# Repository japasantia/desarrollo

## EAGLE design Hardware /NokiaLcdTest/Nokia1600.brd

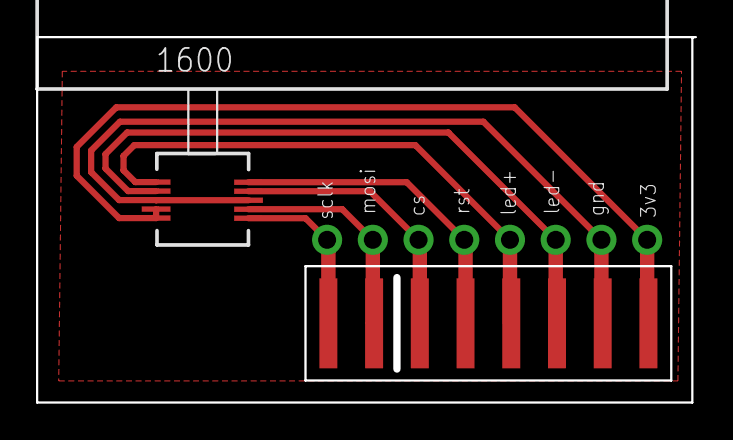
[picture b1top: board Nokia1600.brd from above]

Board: 2 copper layers, 36.6 x 20.3 mm, 3 parts (0 on the bottom side), 8 nets.

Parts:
EDGE1: CARD-EDGE-8P; DUOPLUG-8P-KEYED
JP1: 1X08_ROUND
U$1: NOKIA1600_LCD

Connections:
CLK: EDGE1.1, JP1.1, U$1.1
CS: EDGE1.3, JP1.3, U$1.4
GND: EDGE1.7, JP1.7, U$1.3, U$1.8
LED+: EDGE1.5, JP1.5, U$1.6
LED-: EDGE1.6, JP1.6, U$1.7
RESET: EDGE1.4, JP1.4, U$1.5
SDA: EDGE1.2, JP1.2, U$1.2
VCC: EDGE1.8, JP1.8, U$1.9, U$1.10

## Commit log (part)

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2017-05-26 Respaldo inicial en Desarrollo
    Se abre el repositorio (nuevamente)
2017-05-29 Commit de respaldo
    Se hace commit masivo para respaldo
2017-06-01 Commit respaldo
    - Trabajo en pruebas de librerias VISA
    - Proyectos desarrollo actualizados
2017-06-06 Pruebas para adaptar libreria <linux-gpib> a Java, por medio de JNA. Respaldo
2017-06-10 Commit para sincronizar repositorios y respaldo
    Se han hecho cambios en PC-casa que no ha sido enviados al repositorio remoto.
2017-06-14 Se modifica archivo de proyecto libreria GPIB en Java
    - Modificación en interfaz ILinuxGPIB
2017-06-15 Respaldo, cambio de nombre archivos
2017-06-16 Trabajo en CenditLab, proyecto Communications
    - Modificacion CommunicationAbstractionLayer
2017-06-19 Trabajo en CenditLab
    - Modificaciones en torno a VisaAddress
2017-06-19 Respaldo de archivo VisaAddress.java para resolver problema de sincronia de repos (rebase)
2017-06-20 Trabajo en CenditLab, Communications - VisaAddress - GpibConnection - Excepciones
2017-06-21 Modificaciones en CenditLab.Communications
    Trabajo en capa comunicaciones GPIB
    - GpibConnection
    - VisaAddress
2017-06-26 Modificacion libreria TFT LCD para PIC18
    - Modificacion módulo TftLcdIO para adaptarlo a los puertos de PIC18F4550
    - Definicion de pines
    - Modificacion de rutinas inicializacion
2017-06-29 Modificaciones en firmware PIC
    - Cendit HID bootloader: resuelto problema con boton booloader
    - Modificados algunos proyectos PIC18 USB
2017-06-29 Trabajo en Communications
    - Wrapper libreria VXI11
    - Prueba de conexion exitosa con VXI11
2017-06-30 Actualizacion de Communications en CenditLab
    - Agregados coentarios relativos a libreria VXI11
    - Trabajo en clase Vxi11Connection
2017-07-07 Trabajo en desarrollo: CenditLab + Pic
    - En CenditLab inicia desarrollo adaptadores Visa.
    - Modificaciones a proyecto PIC pic_lcd.
2017-07-11 Se agregan dos proyectos en desarrollo
    - Modificación del proyecto Cendit Hid Bootloader
    - Nuevo proyecto pic_serial_pc: consola serial para la tarjeta CenditBoard
2017-07-14 Trabajo en desarrollo: CenditLab
    - Continua desarrollo librearia Measurments, agregadas nuevas clases
    - Modificaciones en proyectos PIC
    - Se agregan proyectos prueba librerias de comunicacion serial
2017-07-17 Modificaciones en proyectos y limpieza directorios
    - Cambios en pic_lcd
    - Revision PicSerial
    - Revision cendit_hid_bootloader_pc
2017-07-18 Modificacion en proyecto pic_cd
    - Modificacion hecha para pruebas con libreria TFT LCD.
    - Respaldo de proyectos modificados anteriormente
2017-07-20 Modificacion en proyectos: pic_serial y pic_lcd
    - Cambios UI en pic_serial + nuevos comandos para probar libreria LCD
2017-07-20 Trabajo en CenditLab, replanteo de clases
    - Se replantea clase ScpiCommands, 3era prueba
2017-07-21 Modificaciones en CenditLab: Measurements y Communications
    - Se reimportan el proyectos, modificaciones en archivos proyecto, manifiestos.
    - Se refina ScpiCommand3
    - Modificadas clases relativas a Task, solo para poder compilar
2017-07-25 Trabajo en pic_lcd y PicSerial
    - Correcciones en libreria PIC LCD, ahora funciona
    - PicSerial utilidad para pruebas libreria PIC LCD, version inicial
2017-07-25 Se inicia proyecto pic_seial_32
    - Proyecto en Qt 5.2 32 bits.
2017-08-02 Commit respaldo
    - Libreria pic_lcd funcional
2017-08-15 Inicia desarrollo de CenditBoard, tarjeta reducida
2017-08-17 CenditLab, prueba nuevo concepto para organizar tareas y sus datos de in/out
    - Se idea un nuevo concepto para el manejo de datos de las tareas.
    - Clase Value, representa argumento de una tarea.
    - Nueva definicion de interfaz Task (Task2).
2017-08-18 Respaldo ultima hora
    - Proyecto Kicad tarjeta Cendit11713, v2
2017-08-23 Respaldo, trabajo en desarrollo de software+hardware
    - En hardware, tarjeta control puertos Viking (Shift register port exp)
    - En software edición ligera en CenditLab
2017-08-24 Trabajo en desarrollo CenditLab + hardware Cendit11713
    - Modulo Task, se crea clases para menejo de Instrumentos (Instrument)
    - Ediciones de esquematicos Cendit11714 + tarjeta Nokia 1600 LCD
2017-08-30 CenditLab, modulo Communications
    - Se importa modulo Communications
    - Proceso de revision y refactor de clases
    - Se crea instalador para pruebas, inicialmente instala modulo Views
2017-08-31 CenditLab, modulo Communications
    - Prosigue la revision de clases: Gpib + Vxi
    - Manejo de excepciones, creacion clase base CommunicationException
    - Pruebas exitosas
2017-09-05 CenditLab, trabajo GUI modulo Views + nuevos tipos de datos en Task
    - Se agregan vistas para arreglos (ArrayData)
    - Boton para barra de navegacion
    - Se agregan tipo de datos ArrayData en Tasks
2017-09-06 CenditLab, trabajo en Communications + Views
    - Comunications, revision + correcciones correspondientes a Vxi11
    - Views, modificaciones en ArrayDataView
2017-09-08 CenditLab, modulo Views + Tasks
    - En Views se agrega widget para graficos XY
    - En Tasks se corrigen fallas en clase ArrayData
2017-09-12 En CenditLab
    - Se modifica control GraphView para acoplarse con GraphData
    - Se renombran clases
    - Pruebas satisfactorias
2017-09-13 En CenditLab se trabaja en concepto para manejo de session de medicion
    - Se crean clases MeasurementSession y MeasurementStep
    - Pruebas con GUI y vistas
2017-09-14 Commit para respaldo ultima hora
2017-09-18 En CenditLab modificaciones en modulos Tasks + Views
    - Edicion de clases MeasurementSession y MeasurementStep
    - Creacion de objetos view StepsBarView y StepButtonView
    - Creacion de archivos fxml respectivos
2017-09-19 CenditLab + footprints PCB
    - En CenditLab se trabaja en UI Views, se crea ContainerWindow
    - Se realizan ajustes en StepButton y StepsBarView
    - Se crea footprint conector SATA
2017-09-21 CenditLab + esquematicos + PCB
    - En CenditLab creadas clases de vistas (Views)
    - Se crean footprints
2017-09-21 Commit adicional al anterior, respaldo
2017-09-27 CenditLab + Cendit11713 multiples cambios desarrollo software + hardware
    - CenditLab revision + reformulacion + refactor de clases
    - Cendit11713 creacion de footprints + esquematico controlador de teclado
2017-09-28 En CenditLab trabajo en modulo Views
    - Forma mas eficiente de generar vistas
    - Organizacion de vistas en filas y columnas
    - Clases RowContainerView + ColumnContainerView
2017-09-29 Trabajo en CenditLab
    - Clases para el organizacion de vistas en filas-columnas
2017-10-08 Trabajo en CenditLab.Reducido + Cendit11713
    - CenditLab componenets GUI setup frecuencia
    - Cendit11713 esquematicos expansor puerto GPIB
2017-10-09 En CenditLab.Reducido
    - Clases manejo de paneles y valores de frecuencia actualizados
2017-10-10 En CenditLab.Reducido
    - Modificacion y refactor de clases Field (FrequencyValue -> FrequencyField)
2017-10-10 Cendit11713: Trabajo en esquematicos + PCB
    - Se editan esquematicos expansor IO Viking
    - Creada tarjeta PCB adaptador multipuertos
2017-10-13 Trabajo en CenditLab.Reducido + Cendit17713 PCB
    - Clases paneles UI modificados
    - Clases para manejo y validacion de datos
    - PCB expansor puertos Viking
2017-10-16 Trabajo en CenditLab + Cendit11713 PCB
    - Clases UI entrada de ENR + archivos fxml
    - Expansor puertos Viking
    - Controlador teclado capacitivo
2017-10-17 Trabajo en CenditLab.Reducido + Cendit11713 PCB
    - CenditLab clases para manejo de setup ENR
    - Clase field para dato temperatura
    - Edición de PCBs Capacitive Keyboard
    - Edición de esquematico MainBoard con PIC18F4550 DIP
2017-10-19 Para Cendit11713 creacion de footprints
    - Interruptores luminosos
    - Sensor humedad SI70201
    - Sensor de presion MPL3115A2
2017-10-20 Cendit11713 respaldo del trabajo en PCBs
2017-10-20 En CendiLab edicion de archivo UI + Respaldo
    - Edicion de fxl para setup
    - Respaldo de archivos esquematicos + PCB
2017-10-22 CenditLab.Reducido respaldo de archivos
    - Archivos .java EnrSetup, FrequencySetup, TemperatureField
2017-10-24 En CenditLab.Reducido
    - Trabajo en clases FrequencySetup + FrequencySetupView.
    - Pruebas satisfactorias
2017-10-26 En CenditLab.Reducido + respaldo archivos Gerber
    - Se retoman clases de antiguo CenditLab
    - Clases relativas a MeasurementManager + MeasurementStep
    - Vista MeasurementBarView + StepButtonView
    - Se respaldan archivos Gerber
2017-10-27 En CenditLab.Reducido + Respaldo
    - Correccion de clase relativas a FieldsView (FieldInput + Field)
    - Respaldo de archivos Cendit11713 (esquematicos + PCB)
    - Respaldo diseño fuente: creado hoy
2017-10-31 En CenditLab: gestion de proceso de medicion en UI + pruebas
    - Clase que representa sistema-dispositivo NFA (System)
    - Clases que representan pasos de medicion (MeasurementStep)
    - Clases tareas asosciadas a NFA (Task)
2017-10-31 En CenditLab trabajo en vistas para setup
    - Clase SetupContainerView vista para configuracion
    - Nueva organizacion de modulos/directorios
    - Se debio reimportar proyectos
2017-11-01 En CenditLab.Reducido + Cendit11713
    - Clase para manejo setup frecuencia basico (BasicFrequencySetup)
    - Archivo fxml para esta clase
    - Correciones en FieldInput
    - Creada simulacion Multisim para high side driver
2017-11-02 Cendit11713 + aparecen modificadas clases Java
    - Diseño de high side driver simulacion Multisim
    - Aparecen modificadas clases Java BasicFrequencySetup, aunque no se hayan tocado
2017-11-02 En CenditLab.Reducido + Cendit11713
    - Clase para vista generica - contenedor top level (GenericMainView)
    - Simulación de un high side driver Multisim
2017-11-07 En CenditLab.Reducido + respaldo de esquematicos + PCBs
    - Clases vistas para cada paso de medicion
    - Respaldo de archivos Cendit11713 (esquematicos + PCBs)
2017-11-08 En CenditLab.Reducido + Cendit11713
    - Para CenditLab vistas para Steps + fabrica de vistas ComponentViewfactory
    - En Cendit11713 revision PCB VikingPortExpander + Gerber
2017-11-09 En CenditLab.Reducido + respaldo de Cendit11713
    - Clases fabrica de vistas ComponentViewFactory
    - Modificacion de clases MeasurementStep
    - Respaldo de archivos esquematicos + PCBs Cendit11713 (sin editar)
2017-11-10 Revision + correccion en CenditLab.Reducido + respaldo diseño hardware
    - Revisadas clases y archivos fxml + correcciones
    - No se modifican archivos hardware pero se respaldan
2017-11-10 En CenditLab.Reducido + Cendit11713
    - Hardware tarjeta madre opcion 2, esquematico + PCB
    - Software UI vistas de setup + steps
2017-11-13 En CenditLab.Reducido trabajo en clases UI
    - Diseño de clases + fxml UI para Tasks
    - Reorganizacion de directorio de recursos (imagenes + fxml)
    - Pruebas satisfactorias
2017-11-15 En CenditLab + Cendit11713
    - Diseño de clases UI para Steps (TaskExecutionStep)
    - Layout PCB tarjeta madre opcion 2
2017-11-16 En CenditLab correcciones en modulo UI
    - Para aumentar eficiencia
2017-11-22 En CenditLab + Cendit11713: commit masivo
    - Trabajo en clases + fxml UI
    - Trabajo en main board option 2 + correccion tarjeta expansor Viking
2017-11-22 Respaldo y continuacion comit anterior
2017-11-23 Trabajo en CenditLab + Cendit11713
    - Diseño + codigo UI
    - PCBs tarjeta madre + puertos Viking
    - Se generan Gerber para solicitud de prototipos PCB
2017-11-28 En Cendit11713 + respaldo de software
    - Esquematico tarjeta madre con PIC18F45K50
    - Respaldo de software CenditLab
    - Gerber files tarjeta interfaz GPIB
2017-11-29 Respaldo de CenditLab
    - Trabajo en UI
2017-11-30 En CenditLab + Cendit11713
    - Creados footprints de reguladores
    - Respaldo en CenditLab UI
2017-12-12 Respaldo de desarrollo
    - Trabajo en Cendit11713 esquematico exp puertos CD4094
2017-12-13 Cendit 11713 port expander CD4094 + respaldo
    - Inicia esquematico y PCB para IO expander con SR CD4094
    - Respaldo de software
